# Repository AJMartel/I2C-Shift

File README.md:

# I2C-Shift
I2C Shifter for 3.3V and 5V mixed signals
#
I2C shifter panelized.brd is a pcb mutliplied x6 times, the total size of the board is 5x5 cm.

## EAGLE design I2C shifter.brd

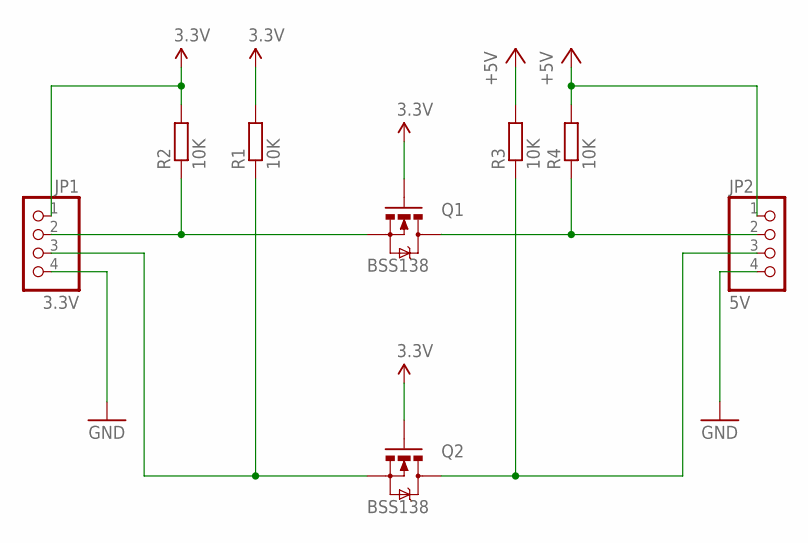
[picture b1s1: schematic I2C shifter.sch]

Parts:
JP1: 3.3V; 1X04
JP2: 5V; 1X04
Q1, Q2: BSS138; SOT23-3
R1, R2, R3, R4: 10K; M1206

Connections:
3.3V: JP1.1, Q1.1 (G), Q2.1 (G), R1.2, R2.2
+5V: JP2.1, R3.2, R4.2
GND: JP1.4, JP2.4
unnamed: JP1.2, Q1.2 (S), R2.1
unnamed: JP1.3, Q2.2 (S), R1.1
unnamed: JP2.2, Q1.3 (D), R4.1
unnamed: JP2.3, Q2.3 (D), R3.1

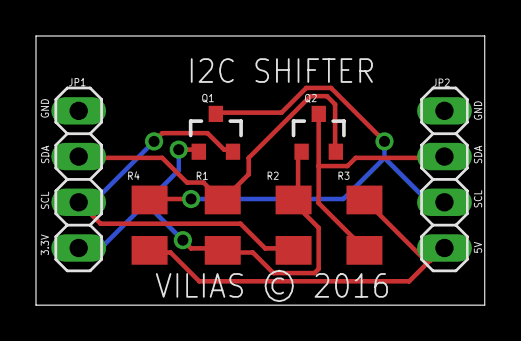
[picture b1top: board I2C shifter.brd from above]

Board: 2 copper layers, 24.9 x 15.0 mm, 8 parts (0 on the bottom side), 7 nets.

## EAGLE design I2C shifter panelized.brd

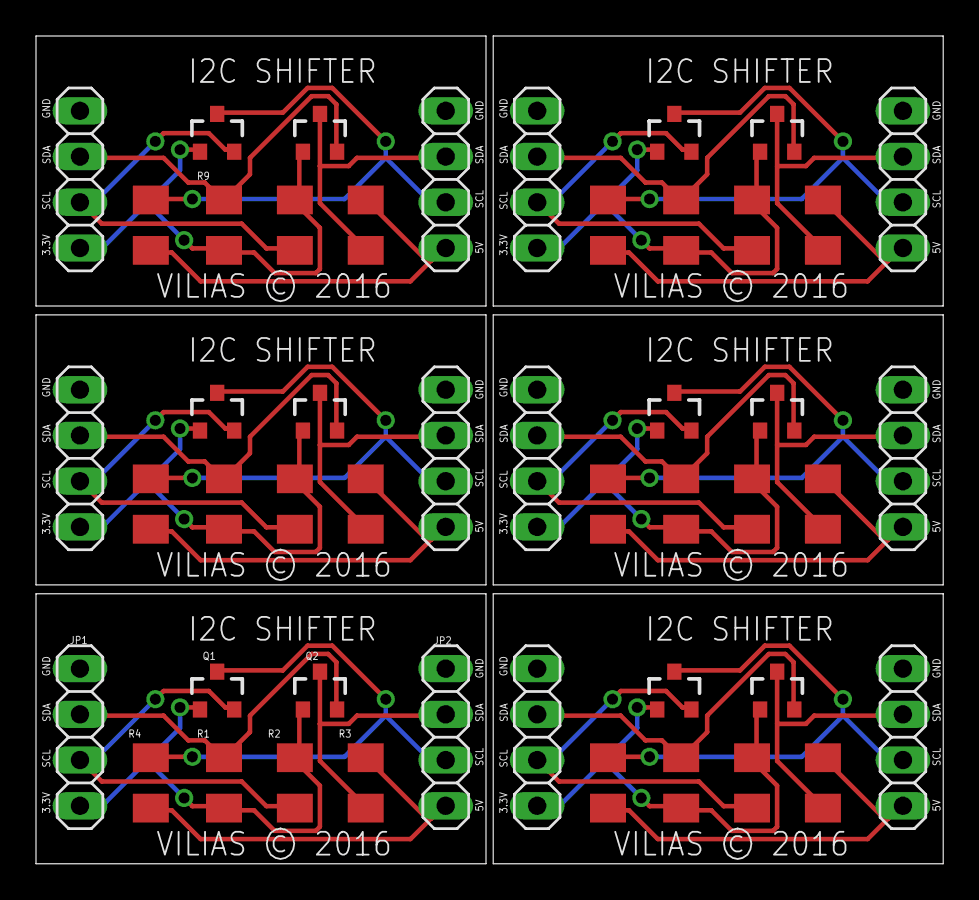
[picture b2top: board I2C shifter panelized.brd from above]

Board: 2 copper layers, 50.4 x 46.0 mm, 48 parts (0 on the bottom side), 42 nets.

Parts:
JP1, JP3, JP5, JP7, JP9, JP11: 3.3V; 1X04
JP2, JP4, JP6, JP8, JP10, JP12: 5V; 1X04
Q1, Q2, Q3, Q4, Q5, Q6, Q7, Q8, Q9, Q10, Q11, Q12: BSS138; SOT23-3
R1, R2, R3, R4, R5, R6, R7, R8, R9, R10, R11, R12, R13, R14, R15, R16, R17, R18, R19, R20, R21, R22, R23, R24: 10K; M1206

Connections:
3.3V: JP1.1, Q1.1, Q2.1, R1.2, R2.2
3.3V1: JP3.1, Q3.1, Q4.1, R5.2, R6.2
3.3V2: JP5.1, Q5.1, Q6.1, R9.2, R10.2
3.3V3: JP7.1, Q7.1, Q8.1, R13.2, R14.2
3.3V4: JP9.1, Q9.1, Q10.1, R17.2, R18.2
3.3V5: JP11.1, Q11.1, Q12.1, R21.2, R22.2
+5V: JP2.1, R3.2, R4.2
+5V1: JP4.1, R7.2, R8.2
+5V2: JP6.1, R11.2, R12.2
+5V3: JP8.1, R15.2, R16.2
+5V4: JP10.1, R19.2, R20.2
+5V5: JP12.1, R23.2, R24.2
GND: JP1.4, JP2.4
GND1: JP3.4, JP4.4
GND2: JP5.4, JP6.4
GND3: JP7.4, JP8.4
GND4: JP9.4, JP10.4
GND5: JP11.4, JP12.4
unnamed: JP1.2, Q1.2, R2.1
unnamed: JP1.3, Q2.2, R1.1
unnamed: JP2.2, Q1.3, R4.1
unnamed: JP2.3, Q2.3, R3.1
unnamed: JP3.2, Q3.2, R6.1
unnamed: JP3.3, Q4.2, R5.1
unnamed: JP4.2, Q3.3, R8.1
unnamed: JP4.3, Q4.3, R7.1
unnamed: JP5.2, Q5.2, R10.1
unnamed: JP5.3, Q6.2, R9.1
unnamed: JP6.2, Q5.3, R12.1
unnamed: JP6.3, Q6.3, R11.1
unnamed: JP7.2, Q7.2, R14.1
unnamed: JP7.3, Q8.2, R13.1
unnamed: JP8.2, Q7.3, R16.1
unnamed: JP8.3, Q8.3, R15.1
unnamed: JP9.2, Q9.2, R18.1
unnamed: JP9.3, Q10.2, R17.1
unnamed: JP10.2, Q9.3, R20.1
unnamed: JP10.3, Q10.3, R19.1
unnamed: JP11.2, Q11.2, R22.1
unnamed: JP11.3, Q12.2, R21.1
unnamed: JP12.2, Q11.3, R24.1
unnamed: JP12.3, Q12.3, R23.1

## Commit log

2016-07-28 :tada: Added .gitattributes
2016-07-28 I2C Shift - Eagle files
    I2C shifter for 3.3V and 5V I2C devices
2016-07-28 Create readme file
    readme file

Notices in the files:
I2C shifter panelized.brd:
VILIAS © 2016
parts and their libraries:
SparkFun-DiscreteSemi: Licensing: Creative Commons ShareAlike 4.0 International - https://creativecommons.org/licenses/by-sa/4.0
